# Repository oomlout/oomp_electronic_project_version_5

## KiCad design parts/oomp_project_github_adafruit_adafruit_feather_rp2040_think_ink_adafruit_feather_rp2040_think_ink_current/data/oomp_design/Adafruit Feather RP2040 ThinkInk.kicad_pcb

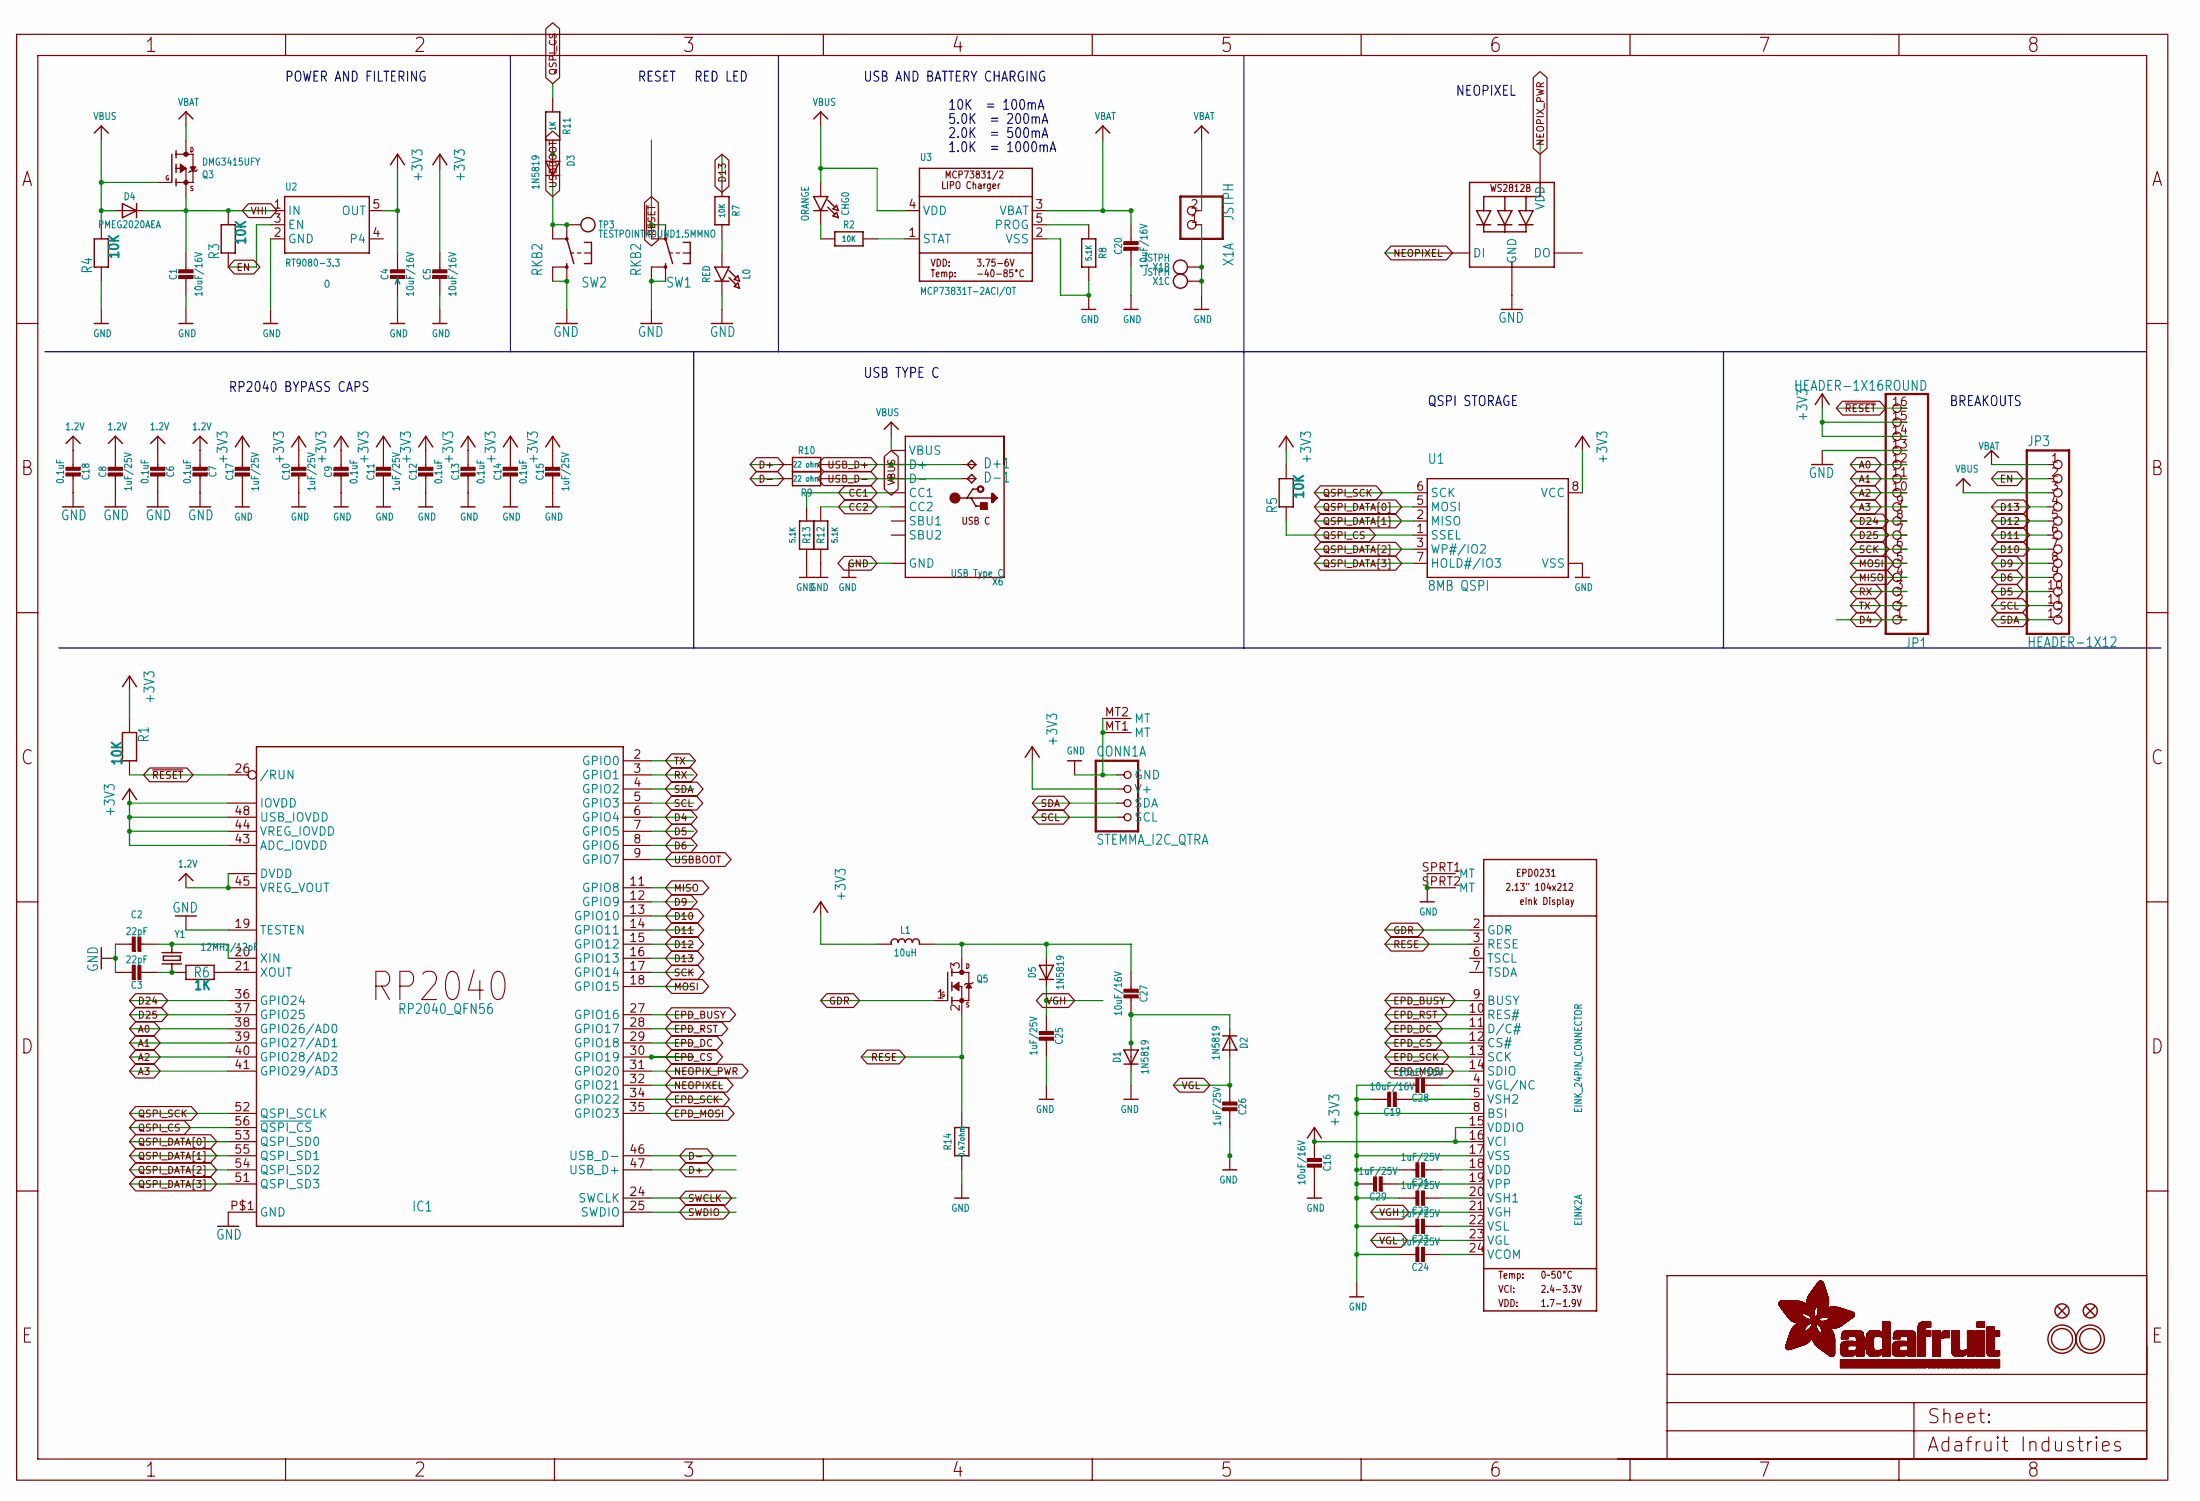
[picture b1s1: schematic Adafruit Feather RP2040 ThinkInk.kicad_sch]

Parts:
C1, C4, C5, C16, C19, C20, C27, C28: 10uF/16V; 0805-NO
C2, C3: 22pF; _0402NO
C6, C7, C9, C12, C13, C14, C18: 0.1uF; _0402NO
C8, C10, C11, C15, C17, C21, C22, C23, C24, C25, C26, C29: 1uF/25V; _0402NO
CHG0: ORANGE; CHIPLED_0603_NOOUTLINE
CONN1: STEMMA_I2C_QTRA; JST_SH4_RA; LCSC C145961
D1, D2, D3, D5: 1N5819; SOD-323_MINI
D4: PMEG2020AEA; SOD-323F
D+1: TPB1,27; B1,27
D-1: TPB1,27; B1,27
EINK2: EINK_24PIN_CONNECTOR; EINK_24PIN
IC1: RP2040_QFN56; QFN56_7MM_REDUCEDEPAD; LCSC C2040
JP1: HEADER-1X16ROUND; 1X16_ROUND
JP3: HEADER-1X12; 1X12_ROUND
L0: RED; CHIPLED_0603_NOOUTLINE
L1: 10uH; INDUCTOR_4X4MM_NR401
LED1: WS2812B_SK6805_1515; SK6805_1515; LCSC C2890035
Q3: DMG3415UFY; DFN2015-3
Q5: IRLML0100; SOT23-WIDE
R1, R2, R3, R4, R5, R7: 10K; _0402NO
R6, R11: 1K; _0402NO
R8, R12, R13: 5.1K; _0402NO
R9, R10: 22 ohm; _0402NO
R14: 0.47ohm; 0603-NO
SW1, SW2: RKB2; BTN_RKB2_4.6X2.8
TP3: TESTPOINTROUND1.5MMNO; TESTPOINT_ROUND_1.5MM_NO
U1: 8MB QSPI; USON8_4X4
U2: RT9080-3.3; SOT23-5; JLC_ROTATION 0
U3: MCP73831T-2ACI/OT; SOT23-5; JLC_ROTATION 270
U$31, U$32: MOUNTINGHOLE2.5; MOUNTINGHOLE_2.5_PLATED
U$34, U$35: FIDUCIAL_1MM
X1: JSTPH; JSTPH2_BATT; LCSC C47647
X6: USB Type C; USB_C_CUSB31-CFM2AX-01-X; LCSC C165948
Y1: 12MHz/12pF; CRYSTAL_2.5X2

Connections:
1.2V: C6.2, C7.2, C8.1, C18.2, IC1.23 (DVDD), IC1.45 (VREG_VOUT), IC1.50 (DVDD)
+3V3: C4.1, C5.1, C9.1, C10.1, C11.1, C12.1, C13.1, C14.1, C15.1, C16.2, C17.1, CONN1.2 (V+), EINK2.15 (VDDIO), EINK2.16 (VCI), IC1.1 (IOVDD), IC1.10 (IOVDD), IC1.22 (IOVDD), IC1.33 (IOVDD), IC1.42 (IOVDD), IC1.43 (ADC_IOVDD), IC1.44 (VREG_IOVDD), IC1.48 (USB_IOVDD), IC1.49 (IOVDD), JP1.14, JP1.15, L1.P$2 (2), R1.1, R5.2, U1.8 (VCC), U2.5 (OUT)
A0: IC1.38 (GPIO26/AD0), JP1.12
A1: IC1.39 (GPIO27/AD1), JP1.11
A2: IC1.40 (GPIO28/AD2), JP1.10
A3: IC1.41 (GPIO29/AD3), JP1.9
CC1: R13.2, X6.A5 (CC1)
CC2: R12.2, X6.B5 (CC2)
D4: IC1.6 (GPIO4), JP1.1
D5: IC1.7 (GPIO5), JP3.10
D6: IC1.8 (GPIO6), JP3.9
D9: IC1.12 (GPIO9), JP3.8
D10: IC1.13 (GPIO10), JP3.7
D11: IC1.14 (GPIO11), JP3.6
D12: IC1.15 (GPIO12), JP3.5
D13: IC1.16 (GPIO13), JP3.4, R7.1
D24: IC1.36 (GPIO24), JP1.8
D25: IC1.37 (GPIO25), JP1.7
D+: IC1.47 (USB_D+), R10.2
D-: IC1.46 (USB_D-), R9.2
EN: JP3.2, R3.1, U2.3 (EN)
EPD_BUSY: EINK2.9 (BUSY), IC1.27 (GPIO16)
EPD_CS: EINK2.12 (CS#), IC1.30 (GPIO19)
EPD_DC: EINK2.11 (D/C#), IC1.29 (GPIO18)
EPD_MOSI: EINK2.14 (SDIO), IC1.35 (GPIO23)
EPD_RST: EINK2.10 (RES#), IC1.28 (GPIO17)
EPD_SCK: EINK2.13 (SCK), IC1.34 (GPIO22)
GDR: EINK2.2 (GDR), Q5.1 (G)
GND: C1.2, C2.1, C3.1, C4.2, C5.2, C6.1, C7.1, C8.2, C9.2, C10.2, C11.2, C12.2, C13.2, C14.2, C15.2, C16.1, C17.2, C18.1, C19.1, C20.2, C21.1, C22.1, C23.1, C24.1, C25.2, C26.2, C28.1, C29.1, CONN1.1 (GND), CONN1.MT1 (MT), CONN1.MT2 (MT), D1.C, EINK2.8 (BSI), EINK2.17 (VSS), EINK2.SPRT1 (MT), EINK2.SPRT2 (MT), IC1.19 (TESTEN), IC1.P$1 (GND), JP1.13, L0.C, LED1.4 (GND), R4.1, R8.2, R12.1, R13.1, R14.2, SW1.B (S), SW1.B' (S1), SW2.B (S), SW2.B' (S1), U1.4 (VSS), U1.PAD (VSS), U2.2 (GND), U3.2 (VSS), X1.1, X1.NC1, X1.NC2, X6.A1B12 (GND), X6.B1A12 (GND)
MISO: IC1.11 (GPIO8), JP1.4
MOSI: IC1.18 (GPIO15), JP1.5
unnamed: CHG0.C, R2.1
unnamed: L0.A, R7.2
unnamed: R2.2, U3.1 (STAT)
unnamed: R8.1, U3.5 (PROG)
unnamed: C2.2, IC1.20 (XIN), Y1.3 (2)
unnamed: C3.2, R6.1, Y1.1
unnamed: IC1.21 (XOUT), R6.2
unnamed: C19.2, EINK2.5 (VSH2)
unnamed: C21.2, EINK2.18 (VDD)
unnamed: C22.2, EINK2.20 (VSH1)
unnamed: C27.2, D1.A, D2.C
unnamed: C27.1, D5.A, L1.P$1 (1), Q5.3 (D)
unnamed: C28.2, EINK2.4 (VGL/NC)
unnamed: C29.2, EINK2.19 (VPP)
unnamed: D3.A, R11.2
unnamed: C23.2, EINK2.22 (VSL)
unnamed: C24.2, EINK2.24 (VCOM)
NEOPIXEL: IC1.32 (GPIO21), LED1.1 (DI)
NEOPIX_PWR: IC1.31 (GPIO20), LED1.2 (VDD)
QSPI_CS: IC1.56 (~QSPI_CS), R5.1, R11.1, U1.1 (SSEL)
QSPI_DATA[0]: IC1.53 (QSPI_SD0), U1.5 (MOSI)
QSPI_DATA[1]: IC1.55 (QSPI_SD1), U1.2 (MISO)
QSPI_DATA[2]: IC1.54 (QSPI_SD2), U1.3 (WP#/IO2)
QSPI_DATA[3]: IC1.51 (QSPI_SD3), U1.7 (HOLD#/IO3)
QSPI_SCK: IC1.52 (QSPI_SCLK), U1.6 (SCK)
RESE: EINK2.3 (RESE), Q5.2 (S), R14.1
RX: IC1.3 (GPIO1), JP1.3
SCK: IC1.17 (GPIO14), JP1.6
SCL: CONN1.4 (SCL), IC1.5 (GPIO3), JP3.11
SDA: CONN1.3 (SDA), IC1.4 (GPIO2), JP3.12
SWCLK: IC1.24 (SWCLK)
SWDIO: IC1.25 (SWDIO)
TX: IC1.2 (GPIO0), JP1.2
USBBOOT: D3.C, IC1.9 (GPIO7), SW2.A, SW2.A' (P1), TP3.P$1
USB_D+: D+1.TP, R10.1, X6.A6 (D+), X6.B6 (D+)
USB_D-: D-1.TP, R9.1, X6.A7 (D-), X6.B7 (D-)
VBAT: C20.1, JP3.1, Q3.3 (D), U3.3 (VBAT), X1.2
VBUS: CHG0.A, D4.A, JP3.3, Q3.1 (G), R4.2, U3.4 (VDD), X6.A4B9 (VBUS), X6.B4A9 (VBUS)
VGH: C25.1, D5.C, EINK2.21 (VGH)
VGL: C26.1, D2.A, EINK2.23 (VGL)
VHI: C1.1, D4.C, Q3.2 (S), R3.2, U2.1 (IN)
~RESET: IC1.26 (/RUN), JP1.16, R1.2, SW1.A, SW1.A' (P1)

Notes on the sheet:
NEOPIXEL
BREAKOUTS
2.0K = 500mA
USB TYPE C
QSPI STORAGE
1.0K = 1000mA
RED LED
5.0K = 200mA
10K = 100mA
POWER AND FILTERING
RESET
USB AND BATTERY CHARGING
RP2040 BYPASS CAPS

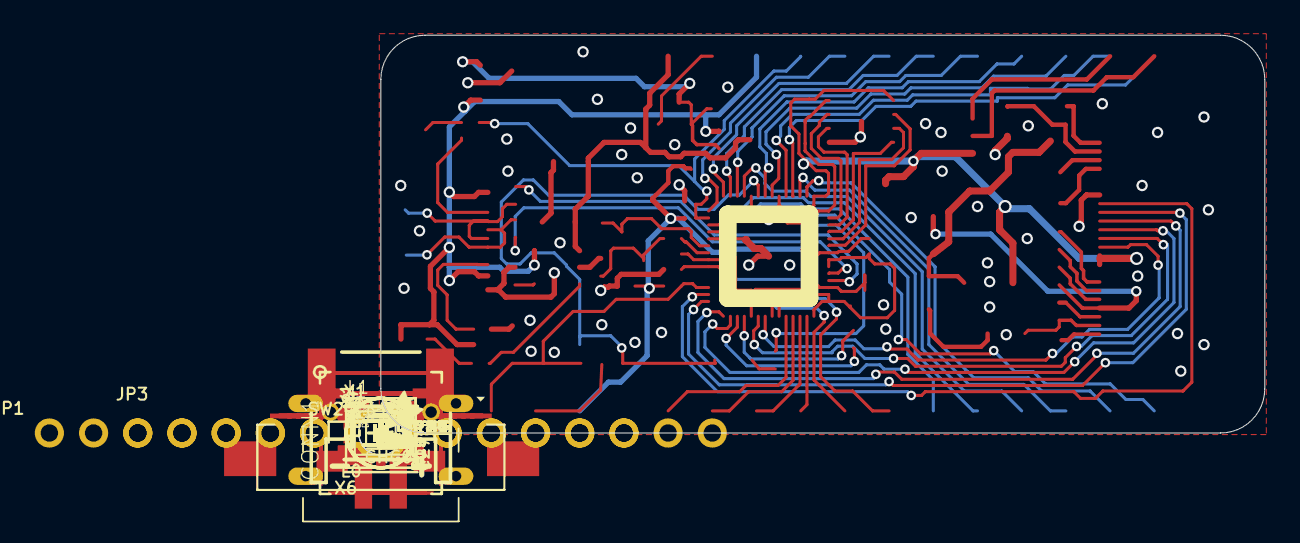
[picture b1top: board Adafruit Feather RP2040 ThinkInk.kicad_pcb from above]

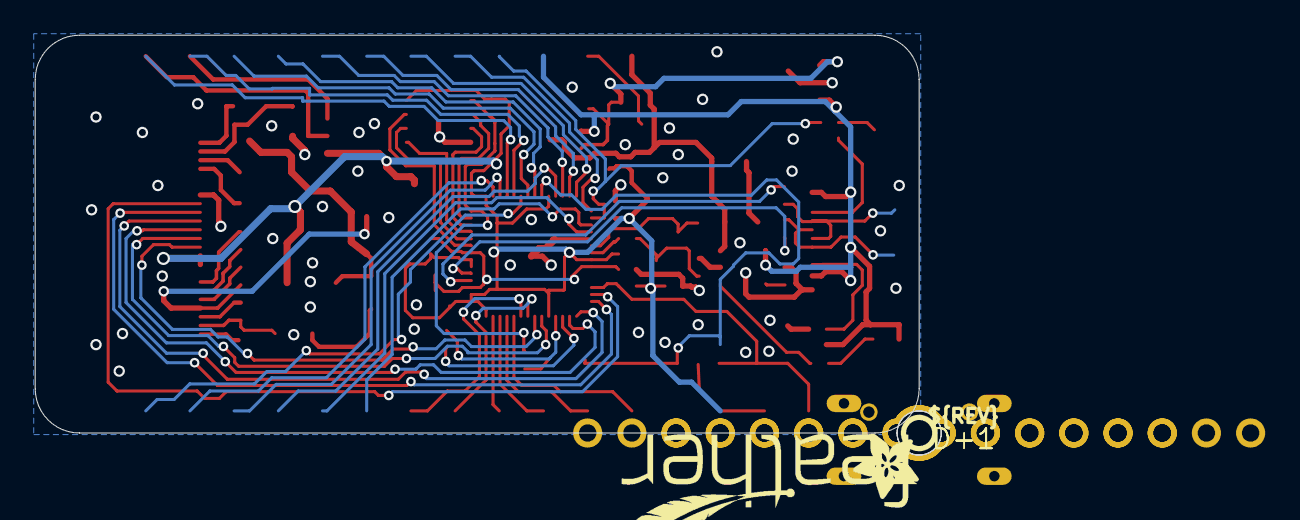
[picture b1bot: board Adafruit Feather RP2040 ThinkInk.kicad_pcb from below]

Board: 2 copper layers, 50.8 x 22.9 mm, 147 parts (38 on the bottom side), 71 nets.

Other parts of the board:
PLABEL0: PLABEL0
PLABEL1: PLABEL1
PLABEL2: PLABEL2
PLABEL3: PLABEL3
PLABEL4: PLABEL4
PLABEL5: PLABEL5
PLABEL6: PLABEL6
PLABEL7: PLABEL7
PLABEL8: PLABEL8
PLABEL9: PLABEL9
PLABEL10: PLABEL10
PLABEL11: PLABEL11
PLABEL12: PLABEL12
PLABEL13: PLABEL13
PLABEL14: PLABEL14
PLABEL15: PLABEL15
PLABEL16: PLABEL16
PLABEL17: PLABEL17
PLABEL18: PLABEL18
PLABEL19: PLABEL19
PLABEL20: PLABEL20
PLABEL21: PLABEL21
PLABEL22: PLABEL22
PLABEL23: PLABEL23
PLABEL24: PLABEL24
PLABEL25: PLABEL25
PLABEL26: PLABEL26
PLABEL27: PLABEL27
PLABEL28: PLABEL28
PLABEL29: PLABEL29
PLABEL30: PLABEL30
PLABEL31: PLABEL31
PLABEL32: PLABEL32
PLABEL33: PLABEL33
PLABEL34: PLABEL34
PLABEL35: PLABEL35
PLABEL36: PLABEL36
PLABEL37: PLABEL37
PLABEL38: PLABEL38
PLABEL39: PLABEL39
PLABEL40: PLABEL40
PLABEL41: PLABEL41
PLABEL42: PLABEL42
PLABEL43: PLABEL43
PLABEL44: PLABEL44
PLABEL45: PLABEL45
PLABEL46: PLABEL46
PLABEL47: PLABEL47
PLABEL48: PLABEL48
PLABEL49: PLABEL49
PLABEL50: PLABEL50
PLABEL51: PLABEL51
PLABEL52: PLABEL52
PLABEL53: PLABEL53
PLABEL54: PLABEL54
PLABEL55: PLABEL55
PLABEL56: PLABEL56
PLABEL57: PLABEL57
PLABEL58: PLABEL58
PLABEL59: PLABEL59
PLABEL60: PLABEL60
PLABEL61: PLABEL61
PLABEL62: PLABEL62
PLABEL63: PLABEL63
PLABEL64: PLABEL64
PLABEL65: PLABEL65
PLABEL66: PLABEL66
U$13: PCBFEAT-REV-040
U$28: ADAFRUIT_2.5MM
U$42: ADAFRUIT_3.5MM
U$46: FEATHERLOGO_MED
UNK_HOLE_0: dummyfp0
UNK_HOLE_1: dummyfp1

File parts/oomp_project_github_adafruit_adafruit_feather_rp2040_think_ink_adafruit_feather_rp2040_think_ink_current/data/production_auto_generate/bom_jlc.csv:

Comment,Designator,Footprint,LCSC Part #
,JP3,Adafruit Feather RP2040 ThinkInk-import-fps:1X12_ROUND,C7501588
,JP1,Adafruit Feather RP2040 ThinkInk-import-fps:1X16_ROUND,C7501270
,U$28,Adafruit Feather RP2040 ThinkInk-import-fps:ADAFRUIT_2.5MM,
,U$42,Adafruit Feather RP2040 ThinkInk-import-fps:ADAFRUIT_3.5MM,
,U$46,Adafruit Feather RP2040 ThinkInk-import-fps:FEATHERLOGO_MED,
,U$13,Adafruit Feather RP2040 ThinkInk-import-fps:PCBFEAT-REV-040,
,PLABEL0,Adafruit Feather RP2040 ThinkInk-import-fps:PLABEL0,
,PLABEL1,Adafruit Feather RP2040 ThinkInk-import-fps:PLABEL1,
,PLABEL10,Adafruit Feather RP2040 ThinkInk-import-fps:PLABEL10,
,PLABEL11,Adafruit Feather RP2040 ThinkInk-import-fps:PLABEL11,
,PLABEL12,Adafruit Feather RP2040 ThinkInk-import-fps:PLABEL12,
,PLABEL13,Adafruit Feather RP2040 ThinkInk-import-fps:PLABEL13,
,PLABEL14,Adafruit Feather RP2040 ThinkInk-import-fps:PLABEL14,
,PLABEL15,Adafruit Feather RP2040 ThinkInk-import-fps:PLABEL15,
,PLABEL16,Adafruit Feather RP2040 ThinkInk-import-fps:PLABEL16,
,PLABEL17,Adafruit Feather RP2040 ThinkInk-import-fps:PLABEL17,
,PLABEL18,Adafruit Feather RP2040 ThinkInk-import-fps:PLABEL18,
,PLABEL19,Adafruit Feather RP2040 ThinkInk-import-fps:PLABEL19,
,PLABEL2,Adafruit Feather RP2040 ThinkInk-import-fps:PLABEL2,
,PLABEL20,Adafruit Feather RP2040 ThinkInk-import-fps:PLABEL20,
,PLABEL21,Adafruit Feather RP2040 ThinkInk-import-fps:PLABEL21,
,PLABEL22,Adafruit Feather RP2040 ThinkInk-import-fps:PLABEL22,
,PLABEL23,Adafruit Feather RP2040 ThinkInk-import-fps:PLABEL23,
,PLABEL24,Adafruit Feather RP2040 ThinkInk-import-fps:PLABEL24,
,PLABEL25,Adafruit Feather RP2040 ThinkInk-import-fps:PLABEL25,
,PLABEL26,Adafruit Feather RP2040 ThinkInk-import-fps:PLABEL26,
,PLABEL27,Adafruit Feather RP2040 ThinkInk-import-fps:PLABEL27,
,PLABEL28,Adafruit Feather RP2040 ThinkInk-import-fps:PLABEL28,
,PLABEL29,Adafruit Feather RP2040 ThinkInk-import-fps:PLABEL29,
,PLABEL3,Adafruit Feather RP2040 ThinkInk-import-fps:PLABEL3,
,PLABEL30,Adafruit Feather RP2040 ThinkInk-import-fps:PLABEL30,
,PLABEL31,Adafruit Feather RP2040 ThinkInk-import-fps:PLABEL31,
,PLABEL32,Adafruit Feather RP2040 ThinkInk-import-fps:PLABEL32,
,PLABEL33,Adafruit Feather RP2040 ThinkInk-import-fps:PLABEL33,
,PLABEL34,Adafruit Feather RP2040 ThinkInk-import-fps:PLABEL34,
,PLABEL35,Adafruit Feather RP2040 ThinkInk-import-fps:PLABEL35,
,PLABEL36,Adafruit Feather RP2040 ThinkInk-import-fps:PLABEL36,
,PLABEL37,Adafruit Feather RP2040 ThinkInk-import-fps:PLABEL37,
,PLABEL38,Adafruit Feather RP2040 ThinkInk-import-fps:PLABEL38,
,PLABEL39,Adafruit Feather RP2040 ThinkInk-import-fps:PLABEL39,
,PLABEL4,Adafruit Feather RP2040 ThinkInk-import-fps:PLABEL4,
,PLABEL40,Adafruit Feather RP2040 ThinkInk-import-fps:PLABEL40,
,PLABEL41,Adafruit Feather RP2040 ThinkInk-import-fps:PLABEL41,
,PLABEL42,Adafruit Feather RP2040 ThinkInk-import-fps:PLABEL42,
,PLABEL43,Adafruit Feather RP2040 ThinkInk-import-fps:PLABEL43,
,PLABEL44,Adafruit Feather RP2040 ThinkInk-import-fps:PLABEL44,
,PLABEL45,Adafruit Feather RP2040 ThinkInk-import-fps:PLABEL45,
,PLABEL46,Adafruit Feather RP2040 ThinkInk-import-fps:PLABEL46,
,PLABEL47,Adafruit Feather RP2040 ThinkInk-import-fps:PLABEL47,
,PLABEL48,Adafruit Feather RP2040 ThinkInk-import-fps:PLABEL48,
,PLABEL49,Adafruit Feather RP2040 ThinkInk-import-fps:PLABEL49,
,PLABEL5,Adafruit Feather RP2040 ThinkInk-import-fps:PLABEL5,
,PLABEL50,Adafruit Feather RP2040 ThinkInk-import-fps:PLABEL50,
,PLABEL51,Adafruit Feather RP2040 ThinkInk-import-fps:PLABEL51,
,PLABEL52,Adafruit Feather RP2040 ThinkInk-import-fps:PLABEL52,
,PLABEL53,Adafruit Feather RP2040 ThinkInk-import-fps:PLABEL53,
,PLABEL54,Adafruit Feather RP2040 ThinkInk-import-fps:PLABEL54,
,PLABEL55,Adafruit Feather RP2040 ThinkInk-import-fps:PLABEL55,
,PLABEL56,Adafruit Feather RP2040 ThinkInk-import-fps:PLABEL56,
,PLABEL57,Adafruit Feather RP2040 ThinkInk-import-fps:PLABEL57,
,PLABEL58,Adafruit Feather RP2040 ThinkInk-import-fps:PLABEL58,
,PLABEL59,Adafruit Feather RP2040 ThinkInk-import-fps:PLABEL59,
,PLABEL6,Adafruit Feather RP2040 ThinkInk-import-fps:PLABEL6,
,PLABEL60,Adafruit Feather RP2040 ThinkInk-import-fps:PLABEL60,
,PLABEL61,Adafruit Feather RP2040 ThinkInk-import-fps:PLABEL61,
,PLABEL62,Adafruit Feather RP2040 ThinkInk-import-fps:PLABEL62,
,PLABEL63,Adafruit Feather RP2040 ThinkInk-import-fps:PLABEL63,
,PLABEL64,Adafruit Feather RP2040 ThinkInk-import-fps:PLABEL64,
,PLABEL65,Adafruit Feather RP2040 ThinkInk-import-fps:PLABEL65,
,PLABEL66,Adafruit Feather RP2040 ThinkInk-import-fps:PLABEL66,
,PLABEL7,Adafruit Feather RP2040 ThinkInk-import-fps:PLABEL7,
,PLABEL8,Adafruit Feather RP2040 ThinkInk-import-fps:PLABEL8,
,PLABEL9,Adafruit Feather RP2040 ThinkInk-import-fps:PLABEL9,
,TP3,Adafruit Feather RP2040 ThinkInk-import-fps:TESTPOINT_ROUND_1.5MM_NO,
0.1uF,"C6,C7,C9,C12,C13,C14,C18",Adafruit Feather RP2040 ThinkInk-import-fps:_0402NO,C60474
0.47ohm,R14,Adafruit Feather RP2040 ThinkInk-import-fps:0603-NO,
10K,"R1,R2,R3,R4,R5,R7",Adafruit Feather RP2040 ThinkInk-import-fps:_0402NO,C2906861
10uF/16V,"C1,C4,C5,C16,C19,C20,C27,C28",Adafruit Feather RP2040 ThinkInk-import-fps:0805-NO,
10uH,L1,Adafruit Feather RP2040 ThinkInk-import-fps:INDUCTOR_4X4MM_NR401,
12MHz/12pF,Y1,Adafruit Feather RP2040 ThinkInk-import-fps:CRYSTAL_2.5X2,
1K,"R6,R11",Adafruit Feather RP2040 ThinkInk-import-fps:_0402NO,C2906864
1N5819,"D1,D2,D3,D5",Adafruit Feather RP2040 ThinkInk-import-fps:SOD-323_MINI,
1uF/25V,"C8,C10,C11,C15,C17,C21,C22,C23,C24,C25,C26,C29",Adafruit Feather RP2040 ThinkInk-import-fps:_0402NO,C2887021
22 ohm,"R9,R10",Adafruit Feather RP2040 ThinkInk-import-fps:_0402NO,C114765
22pF,"C2,C3",Adafruit Feather RP2040 ThinkInk-import-fps:_0402NO,C106203
5.1K,"R8,R12,R13",Adafruit Feather RP2040 ThinkInk-import-fps:_0402NO,C25905
8MB QSPI,U1,Adafruit Feather RP2040 ThinkInk-import-fps:USON8_4X4,
DMG3415UFY,Q3,Adafruit Feather RP2040 ThinkInk-import-fps:DFN2015-3,
EINK_24PIN_CONNECTOR,EINK2,Adafruit Feather RP2040 ThinkInk-import-fps:EINK_24PIN,
FIDUCIAL_1MM,"U$34,U$35",Adafruit Feather RP2040 ThinkInk-import-fps:FIDUCIAL_1MM,
IRLML0100,Q5,Adafruit Feather RP2040 ThinkInk-import-fps:SOT23-WIDE,
JSTPH,X1,Adafruit Feather RP2040 ThinkInk-import-fps:JSTPH2_BATT,
MCP73831T-2ACI/OT,U3,Adafruit Feather RP2040 ThinkInk-import-fps:SOT23-5,
ORANGE,CHG0,Adafruit Feather RP2040 ThinkInk-import-fps:CHIPLED_0603_NOOUTLINE,
PMEG2020AEA,D4,Adafruit Feather RP2040 ThinkInk-import-fps:SOD-323F,
RED,L0,Adafruit Feather RP2040 ThinkInk-import-fps:CHIPLED_0603_NOOUTLINE,
RKB2,"SW1,SW2",Adafruit Feather RP2040 ThinkInk-import-fps:BTN_RKB2_4.6X2.8,
RP2040_QFN56,IC1,Adafruit Feather RP2040 ThinkInk-import-fps:QFN56_7MM_REDUCEDEPAD,
RT9080-3.3,U2,Adafruit Feather RP2040 ThinkInk-import-fps:SOT23-5,
STEMMA_I2C_QTRA,CONN1,Adafruit Feather RP2040 ThinkInk-import-fps:JST_SH4_RA,
"TPB1,27","D+1,D-1","Adafruit Feather RP2040 ThinkInk-import-fps:B1,27",
USB Type C,X6,Adafruit Feather RP2040 ThinkInk-import-fps:USB_C_CUSB31-CFM2AX-01-X,
WS2812B_SK6805_1515,LED1,Adafruit Feather RP2040 ThinkInk-import-fps:SK6805_1515,

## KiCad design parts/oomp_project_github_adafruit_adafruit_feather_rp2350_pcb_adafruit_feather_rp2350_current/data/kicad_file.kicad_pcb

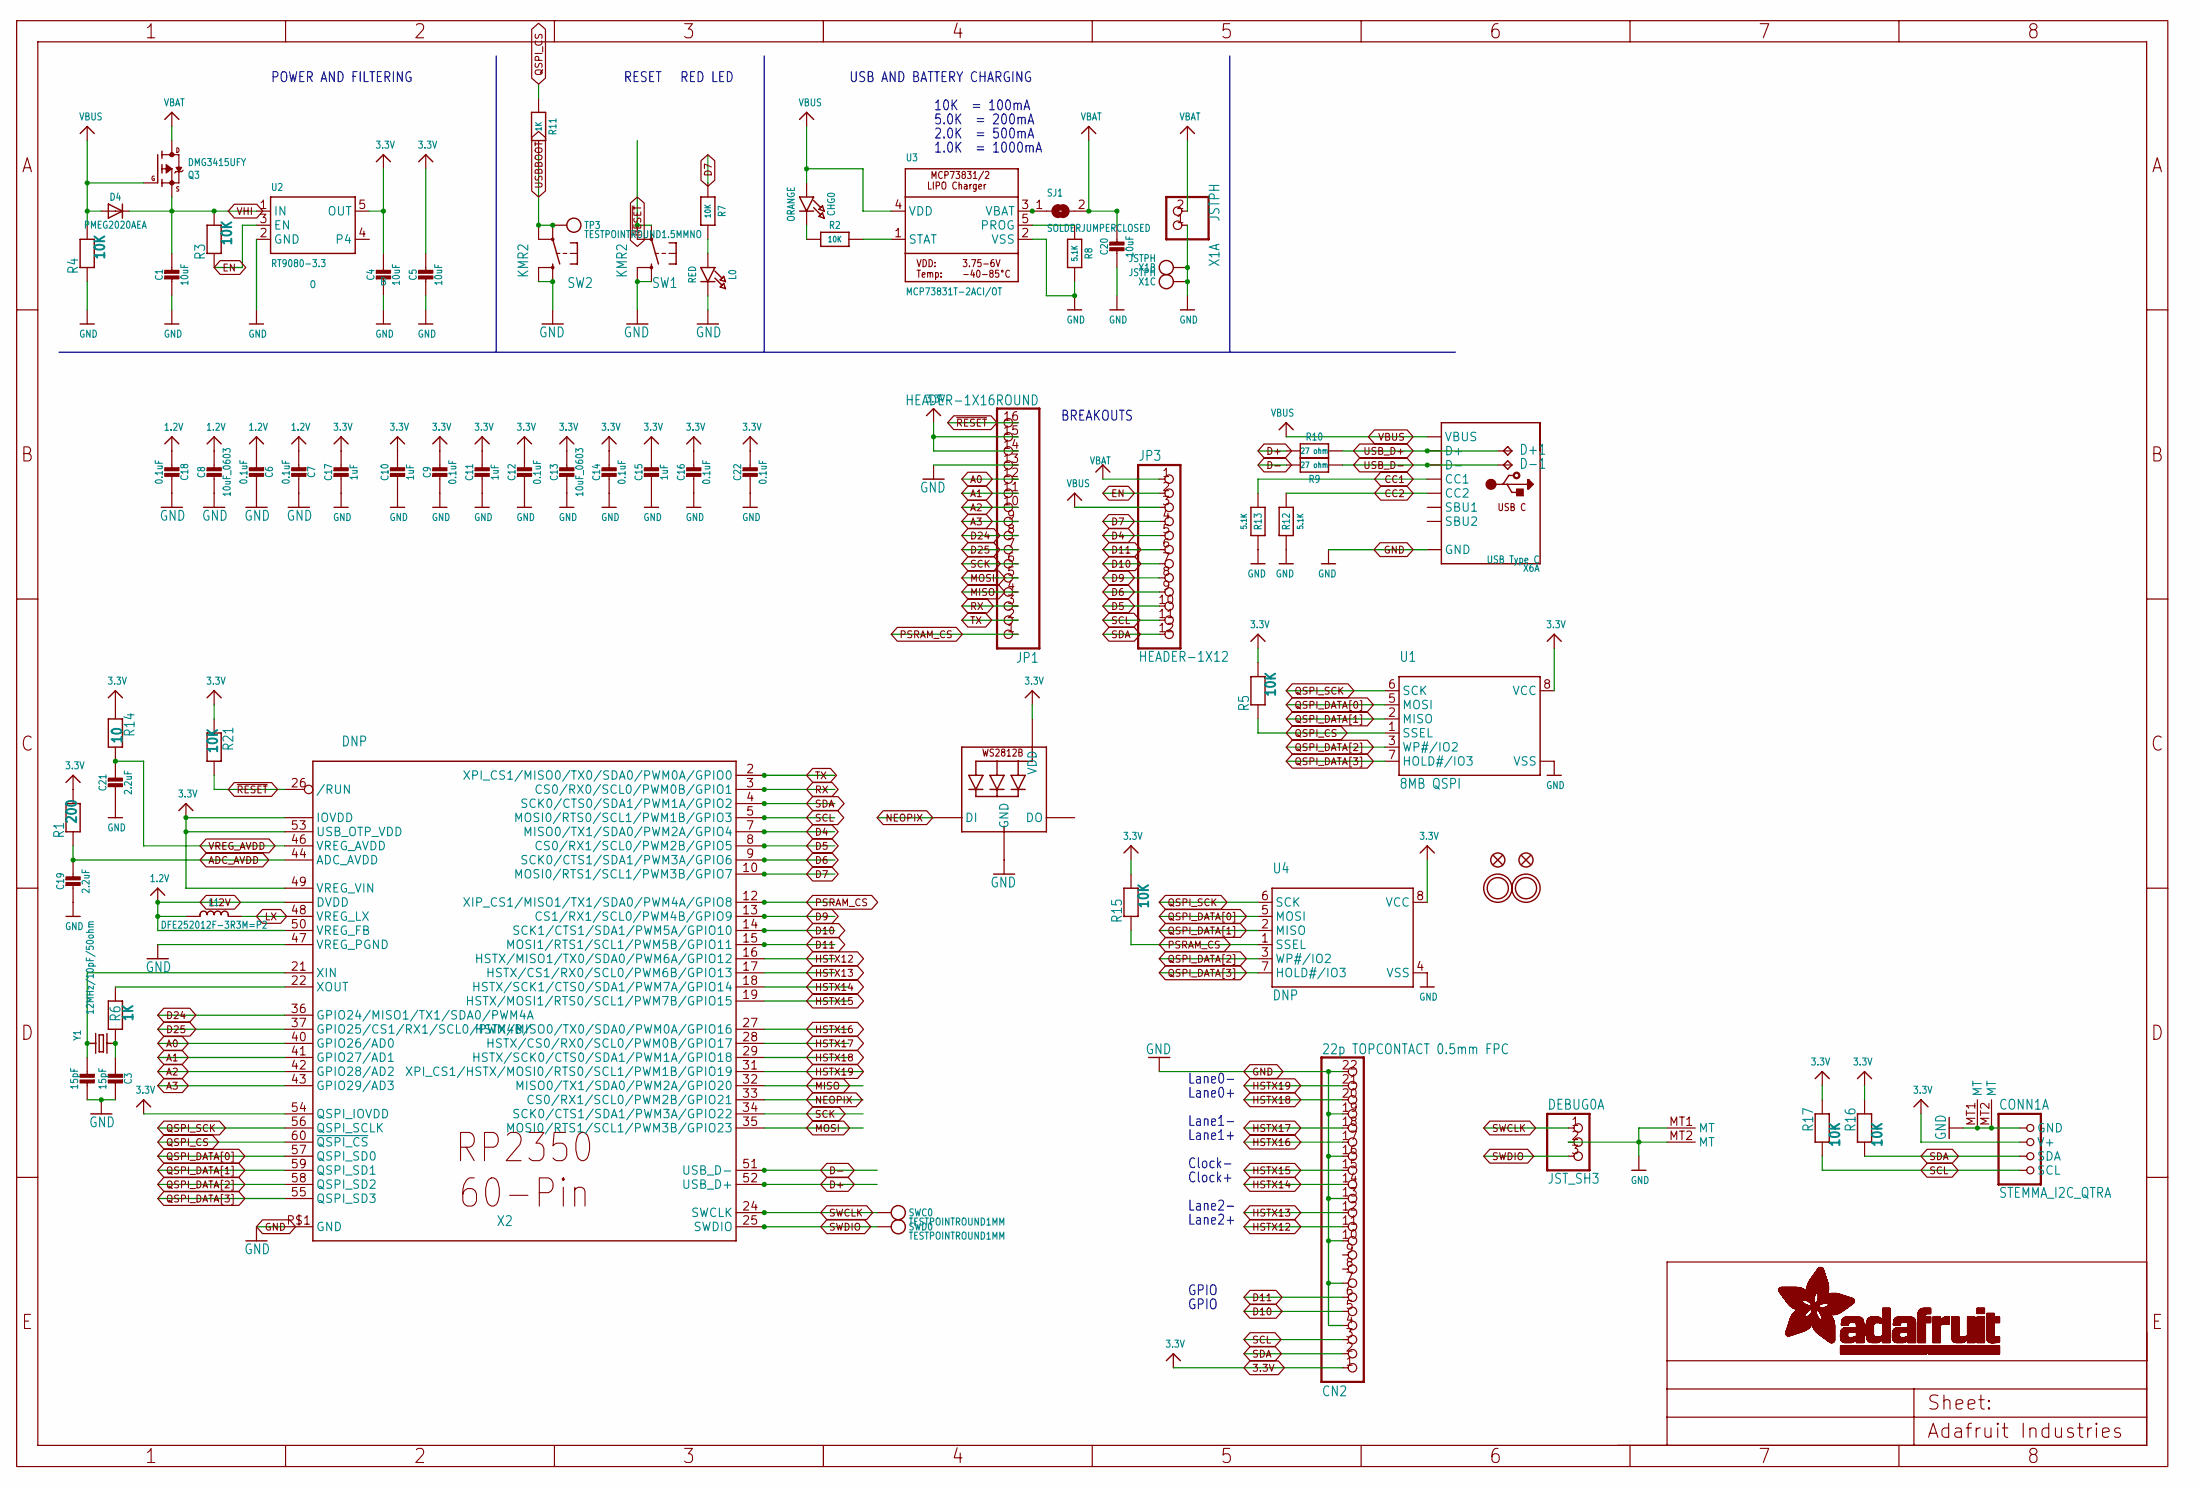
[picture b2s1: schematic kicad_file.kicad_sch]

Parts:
C1, C4, C20: 10uF; 0805-NO
C2, C3: 15pF; _0402NO
C5: 10uF; 0603-NO
C6, C7, C9, C12, C14, C16, C18, C22: 0.1uF; _0402NO
C8, C13: 10uF_0603; _0603MP
C10, C11, C15, C17: 1uF; _0402NO
C19, C21: 2.2uF; _0402NO
CHG0: ORANGE; CHIPLED_0603_NOOUTLINE
CN2: 22p TOPCONTACT 0.5mm FPC; FPC_22PIN
CONN1: STEMMA_I2C_QTRA; JST_SH4_RA; LCSC C145961
D4: PMEG2020AEA; SOD-323F
D+1: TPB1,27; B1,27
D-1: TPB1,27; B1,27
DEBUG0: JST_SH3; JST_SH3_RA
JP1: HEADER-1X16ROUND; 1X16_ROUND
JP3: HEADER-1X12; 1X12_ROUND
L0: RED; CHIPLED_0603_NOOUTLINE
L1: DFE252012F-3R3M=P2; INDUCTOR_1007
LED1: WS2812B_SK6805_1515; SK6805_1515; LCSC C2890035
Q3: DMG3415UFY; DFN2015-3
R1: 200; _0402NO
R2, R3, R4, R5, R7, R15, R16, R17, R21: 10K; _0402NO
R6, R11: 1K; _0402NO
R8, R12, R13: 5.1K; _0402NO
R9, R10: 27 ohm; _0402NO
R14: 10; _0402NO
SJ1: SOLDERJUMPERCLOSED; SOLDERJUMPER_CLOSEDWIRE
SW1, SW2: KMR2; BTN_RKB2_4.6X2.8
SWC0: TESTPOINTROUND1MM; TESTPOINT_ROUND_1MM
SWD0: TESTPOINTROUND1MM; TESTPOINT_ROUND_1MM
TP3: TESTPOINTROUND1.5MMNO; TESTPOINT_ROUND_1.5MM_NO
U1: 8MB QSPI; USON8_4X4
U2: RT9080-3.3; SOT23-5; JLC_ROTATION 0
U3: MCP73831T-2ACI/OT; SOT23-5; JLC_ROTATION 0
U4: DNP; SOIC8_150MIL
U$31, U$32: MOUNTINGHOLE2.5; MOUNTINGHOLE_2.5_PLATED
U$34, U$35: FIDUCIAL_1MM
X1: JSTPH; JSTPH2_BATT; LCSC C47647
X2: DNP; QFN60_7MM_REDUCEDEPAD
X6: USB Type C; USB_C_CUSB31-CFM2AX-01-X; LCSC C165948
Y1: 12MHz/10pF/50ohm; CRYSTAL_2.5X2

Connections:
1.2V: C6.2, C7.2, C8.1, C18.2, L1.P$1 (1), X2.6 (DVDD), X2.23 (DVDD), X2.39 (DVDD), X2.50 (VREG_FB)
3.3V: C4.1, C5.1, C9.1, C10.1, C11.1, C12.1, C13.1, C14.1, C15.1, C16.1, C17.1, C22.1, CN2.1, CONN1.2 (V+), JP1.14, JP1.15, LED1.2 (VDD), R1.2, R5.2, R14.1, R15.2, R16.1, R17.1, R21.1, U1.8 (VCC), U2.5 (OUT), U4.8 (VCC), X2.1 (IOVDD), X2.11 (IOVDD), X2.20 (IOVDD), X2.30 (IOVDD), X2.38 (IOVDD), X2.45 (IOVDD), X2.49 (VREG_VIN), X2.53 (USB_OTP_VDD), X2.54 (QSPI_IOVDD)
A0: JP1.12, X2.40 (GPIO26/AD0)
A1: JP1.11, X2.41 (GPIO27/AD1)
A2: JP1.10, X2.42 (GPIO28/AD2)
A3: JP1.9, X2.43 (GPIO29/AD3)
ADC_AVDD: C19.1, R1.1, X2.44 (ADC_AVDD)
CC1: R13.2, X6.A5 (CC1)
CC2: R12.2, X6.B5 (CC2)
D4: JP3.5, X2.7 (MISO0/TX1/SDA0/PWM2A/GPIO4)
D5: JP3.10, X2.8 (CS0/RX1/SCL0/PWM2B/GPIO5)
D6: JP3.9, X2.9 (SCK0/CTS1/SDA1/PWM3A/GPIO6)
D7: JP3.4, R7.1, X2.10 (MOSI0/RTS1/SCL1/PWM3B/GPIO7)
D9: JP3.8, X2.13 (CS1/RX1/SCL0/PWM4B/GPIO9)
D10: CN2.5, JP3.7, X2.14 (SCK1/CTS1/SDA1/PWM5A/GPIO10)
D11: CN2.6, JP3.6, X2.15 (MOSI1/RTS1/SCL1/PWM5B/GPIO11)
D24: JP1.8, X2.36 (GPIO24/MISO1/TX1/SDA0/PWM4A)
D25: JP1.7, X2.37 (GPIO25/CS1/RX1/SCL0/PWM4B/)
D+: R10.2, X2.52 (USB_D+)
D-: R9.2, X2.51 (USB_D-)
EN: JP3.2, R3.1, U2.3 (EN)
GND: C1.2, C2.1, C3.1, C4.2, C5.2, C6.1, C7.1, C8.2, C9.2, C10.2, C11.2, C12.2, C13.2, C14.2, C15.2, C16.2, C17.2, C18.1, C19.2, C20.2, C21.2, C22.2, CN2.4, CN2.7, CN2.10, CN2.13, CN2.16, CN2.19, CN2.22, CONN1.1 (GND), CONN1.MT1 (MT), CONN1.MT2 (MT), DEBUG0.2, DEBUG0.MT1 (MT), DEBUG0.MT2 (MT), JP1.13, L0.C, LED1.4 (GND), R4.1, R8.2, R12.1, R13.1, SW1.B (S), SW1.B' (S1), SW2.B (S), SW2.B' (S1), U1.4 (VSS), U1.PAD (VSS), U2.2 (GND), U3.2 (VSS), U4.4 (VSS), X1.1, X1.NC1, X1.NC2, X2.47 (VREG_PGND), X2.P$1 (GND), X6.A1B12 (GND), X6.B1A12 (GND)
HSTX12: CN2.11, X2.16 (HSTX/MISO1/TX0/SDA0/PWM6A/GPIO12)
HSTX13: CN2.12, X2.17 (HSTX/CS1/RX0/SCL0/PWM6B/GPIO13)
HSTX14: CN2.14, X2.18 (HSTX/SCK1/CTS0/SDA1/PWM7A/GPIO14)
HSTX15: CN2.15, X2.19 (HSTX/MOSI1/RTS0/SCL1/PWM7B/GPIO15)
HSTX16: CN2.17, X2.27 (HSTX/MISO0/TX0/SDA0/PWM0A/GPIO16)
HSTX17: CN2.18, X2.28 (HSTX/CS0/RX0/SCL0/PWM0B/GPIO17)
HSTX18: CN2.20, X2.29 (HSTX/SCK0/CTS0/SDA1/PWM1A/GPIO18)
HSTX19: CN2.21, X2.31 (XPI_CS1/HSTX/MOSI0/RTS0/SCL1/PWM1B/GPIO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)
LX: L1.P$2 (2), X2.48 (VREG_LX)
MISO: JP1.4, X2.32 (MISO0/TX1/SDA0/PWM2A/GPIO20)
MOSI: JP1.5, X2.35 (MOSI0/RTS1/SCL1/PWM3B/GPIO23)
unnamed: CHG0.C, R2.1
unnamed: L0.A, R7.2
unnamed: R2.2, U3.1 (STAT)
unnamed: R8.1, U3.5 (PROG)
unnamed: C2.2, X2.21 (XIN), Y1.3 (2)
unnamed: C3.2, R6.1, Y1.1
unnamed: R6.2, X2.22 (XOUT)
unnamed: SJ1.1, U3.3 (VBAT)
NEOPIX: LED1.1 (DI), X2.33 (CS0/RX1/SCL0/PWM2B/GPIO21)
PSRAM_CS: JP1.1, R15.1, U4.1 (SSEL), X2.12 (XIP_CS1/MISO1/TX1/SDA0/PWM4A/GPIO8)
QSPI_CS: R5.1, R11.1, U1.1 (SSEL), X2.60 (~QSPI_CS)
QSPI_DATA[0]: U1.5 (MOSI), U4.5 (MOSI), X2.57 (QSPI_SD0)
QSPI_DATA[1]: U1.2 (MISO), U4.2 (MISO), X2.59 (QSPI_SD1)
QSPI_DATA[2]: U1.3 (WP#/IO2), U4.3 (WP#/IO2), X2.58 (QSPI_SD2)
QSPI_DATA[3]: U1.7 (HOLD#/IO3), U4.7 (HOLD#/IO3), X2.55 (QSPI_SD3)
QSPI_SCK: U1.6 (SCK), U4.6 (SCK), X2.56 (QSPI_SCLK)
RX: JP1.3, X2.3 (CS0/RX0/SCL0/PWM0B/GPIO1)
SCK: JP1.6, X2.34 (SCK0/CTS1/SDA1/PWM3A/GPIO22)
SCL: CN2.3, CONN1.4 (SCL), JP3.11, R17.2, X2.5 (MOSI0/RTS0/SCL1/PWM1B/GPIO3)
SDA: CN2.2, CONN1.3 (SDA), JP3.12, R16.2, X2.4 (SCK0/CTS0/SDA1/PWM1A/GPIO2)
SWCLK: DEBUG0.1, SWC0.P$1, X2.24 (SWCLK)
SWDIO: DEBUG0.3, SWD0.P$1, X2.25 (SWDIO)
TX: JP1.2, X2.2 (XPI_CS1/MISO0/TX0/SDA0/PWM0A/GPIO0)
USBBOOT: R11.2, SW2.A, SW2.A' (P1), TP3.P$1
USB_D+: D+1.TP, R10.1, X6.A6 (D+), X6.B6 (D+)
USB_D-: D-1.TP, R9.1, X6.A7 (D-), X6.B7 (D-)
VBAT: C20.1, JP3.1, Q3.3 (D), SJ1.2, X1.2
VBUS: CHG0.A, D4.A, JP3.3, Q3.1 (G), R4.2, U3.4 (VDD), X6.A4B9 (VBUS), X6.B4A9 (VBUS)
VHI: C1.1, D4.C, Q3.2 (S), R3.2, U2.1 (IN)
VREG_AVDD: C21.1, R14.2, X2.46 (VREG_AVDD)
~RESET: JP1.16, R21.2, SW1.A, SW1.A' (P1), X2.26 (/RUN)

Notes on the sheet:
GPIO
RED LED
Lane1+
5.0K = 200mA
Lane1-
POWER AND FILTERING
10K = 100mA
Lane2-
USB AND BATTERY CHARGING
RESET
Lane0+
Clock+
Lane2+
1.0K = 1000mA
Clock-
BREAKOUTS
2.0K = 500mA
Lane0-
